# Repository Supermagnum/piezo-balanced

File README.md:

A small board that uses a LSK389B dual N channel Jfet,and a LSK170B N channel Jfet for preamplifier and impedance matching of two piezo electric crystals wired in balance.
Those J-FET's are ultra low noise components.
Please use 0,5 W metal film resistors with 1% tolerance or better and audio quality capacitors.
C0G (NP0) or X7R capacitors is very good.

The circuit may benefit from a Zobel network, that is a 680 pF capacitor and a 150 ohms resistor in series between pin 2 and 3 on the output or the input connector. It should avoid high frequency oscillation in a long cable.

It has balanced input and output.
That should minimize electric noise picked up from the environment.
One can read more about that here:
https://en.m.wikipedia.org/wiki/Balanced_audio

It's for +48 volt phantom power.
https://en.m.wikipedia.org/wiki/Phantom_power

+48 volt phantom power supply with mono headphone jack, runs on 9V battery:
https://github.com/Supermagnum/48power

PCB:
https://aisler.net/p/UJQSALGW
Note: Aisler does not carry LSK170B in  TO-92 3L or LSK389B in TO-71-6 .

PCB dimentions:
https://github.com/Supermagnum/piezo-balanced/blob/main/dimentions.png

Component side picture:
https://raw.githubusercontent.com/Supermagnum/piezo-balanced/main/piezo-jfet.jpg

Back side picture:
https://github.com/Supermagnum/piezo-balanced/raw/main/piezo-jfet2.jpg

Electronic diagram with component values, it also shows how to wire the crystals:
https://github.com/Supermagnum/piezo-balanced/blob/main/piezo-jfet.pdf

Gerber files for production of the PCB:
https://github.com/Supermagnum/piezo-balanced/tree/main/gerbers

Simulation in Ltspice:

Ltspice setup:
https://github.com/Supermagnum/piezo-balanced/blob/main/Ltspice-setup.png

Frequency response:
https://github.com/Supermagnum/piezo-balanced/blob/main/response.png

LSK170B datasheet:
https://www.linearsystems.com/lsdata/datasheets/201110%20-LSK170%20Rev%20A17%20dated%202017%2008%2028.pdf

Complete LSK389B datasheet:
https://linearsystems.com/lsdata/datasheets/Copy_201122%20-%20LSK389%20Datasheet%20Rev%20A24%202020%2001%2007.pdf

Digikey does not sell LSK389B or LSK170B in single or dual orders.
The 40 ohm resistor is also not sold by digikey .
Alternatively two 80 ohm resistors in parallel can be used.
That gives 40 ohm.

But, these does have LSK389B !
https://store.nacsemi.com/Products/Detail?stock=LIS000000001342

LSK170B:
https://store.nacsemi.com/products/detail?part=LSK170B-TO-92&stock=LIS000000000640

Picture of a piezoelectric disc, with red wire for positive polarity and black for negative:
https://github.com/Supermagnum/piezo-balanced/blob/main/Piezo-element-6.jpg

Why: 
The problem with piezo guitar pickups and piezoelectric crystals is that they are not well matched to typical audio inputs.
By their nature they can generate a lot of signal, but they cannot drive a 50 kilohm typical line input. 
The pickup needs to work into a much higher impedance, typically 1 megohm or so.

So what to people do? 
They go and plug a piezoelectric disks output directly into the line input of their recorder, 
typical impedance 50k, or the plug-in-power mic input of their recorder, typical impedance about 7k,
and they start to bitch and moan that this damn thing sounds tinny. 
Which is does ! But they don't understand why!

The reason why these devices often sound tinny is because the piezo sensor 
presents its signal through a series capacitance which is small, typically 15nF or less. 
When wired to a normal 50 kilohm line input this forms a high-pass filter, which eliminates the bass.

This circuit board solves that, and amplifies the signal around 15~30 dB. 
How many dB it amplifies is dependent on the impedance on the recording equipment.

I am getting 24 dB with 10K ohm impedance of the recorder ( simulated ).

If R4, R8 and R12 is removed,and jumpers installed in their place, the gain is 38 dB with 10K impedance.
You get more with higher impedance, expect 40 dB with 40K impedance of the recorders input.

It's fairly easy and straight forward to solder the components to the circuit board,
a nice pointy soldering iron, solder, a magnifying glass, and a ohm or multimeter is all that is needed.
Of course one needs a suitable metal box, and the circuit boards components
must not come in contact with the metal box. 
That will cause short circuit, so it's best mounted on stand offs.
Also, use the magnifying glass to check that no one of the soldering pads has been bridged.

It can be used for a reverb plate, listening to the insides of a engine,recording the sound of vibrating things.
You will need two piezoelectric disks for that, mounted in a metal box. 
Non electric conductive super glue is useable for that. Just glue them to a flat surface.
The piezoelectric disks should be electrically insulated from the metal box.

Mechanics may even use it to discover trouble with bearings or other mechanisms not easily opened,
but it will need a dedicated +48 volts phantom power supply with headphone jack for that specific usage. 

Of course one can use a recorder like a tascam dr40x, as long as it can supply +48 volt phantom power, and has a headphone jack for monitoring.

They usually have a 3 pin XLR plug.
Those are wired up like this:
https://github.com/Supermagnum/piezo-balanced/blob/main/XLR%2BConnector%2BPinout%2BDiagram%2BRear%2BPin%2B2%2BHot%2Bv2%2Bgreen__01.jpg

NOTE:  
The XLR 3 pin plug has a solder lug for the shield for a reason.
It is my opinion that a shielded cable with 3 conductors inside is the best.
Suggested cable: Digi-Key Part Number: 30-00910-5-ND

A good set of headphones or ear protection with built in speakers will keep out unwanted sounds or noise.

Should also work nice with hydrophones.
PZT-5H tubes is best for that.

For hydrophone usage:
The two piezoelectric tubes elements needs to be encapsulated in Ecopoxy Flowcast epoxy, with as little thickness to the outside of the piezoelectric tubes as possible. 
Commercial ones uses kerosene oil, so olive oil or sunflower oil is a great alternative as it will not pollute the environment if any leaks occurs.
A streamlined bulb should be nice for that. The more streamlined, the less water flow noise. 

Some interesting ideas can be found in:
https://github.com/Supermagnum/piezo-balanced/blob/main/Barlow-et-al-2008-HydrophoneConstruction_TM-417.pdf
Note: Ecopoxy Flowcast does not need any vacuum, just a mold and a way to hold the piezoelectric tubes centered.
It's also safer to work with.
Of course two piezoelectric disks inside something waterproof that can handle the water pressure is also useable.

Some methods of mounting a piezoelectric disk can be found here: https://locusonus.org/wiki/index.php?page=Hydrophone.en

Made with:
http://www.kicad.org/

KiCad uses an integrated environment for all of the stages of the design process: Schematic capture, PCB layout, Gerber file generation/visualization, and library editing.

KiCad is a cross-platform program, and of curse free!

The PCB board is tested and works.

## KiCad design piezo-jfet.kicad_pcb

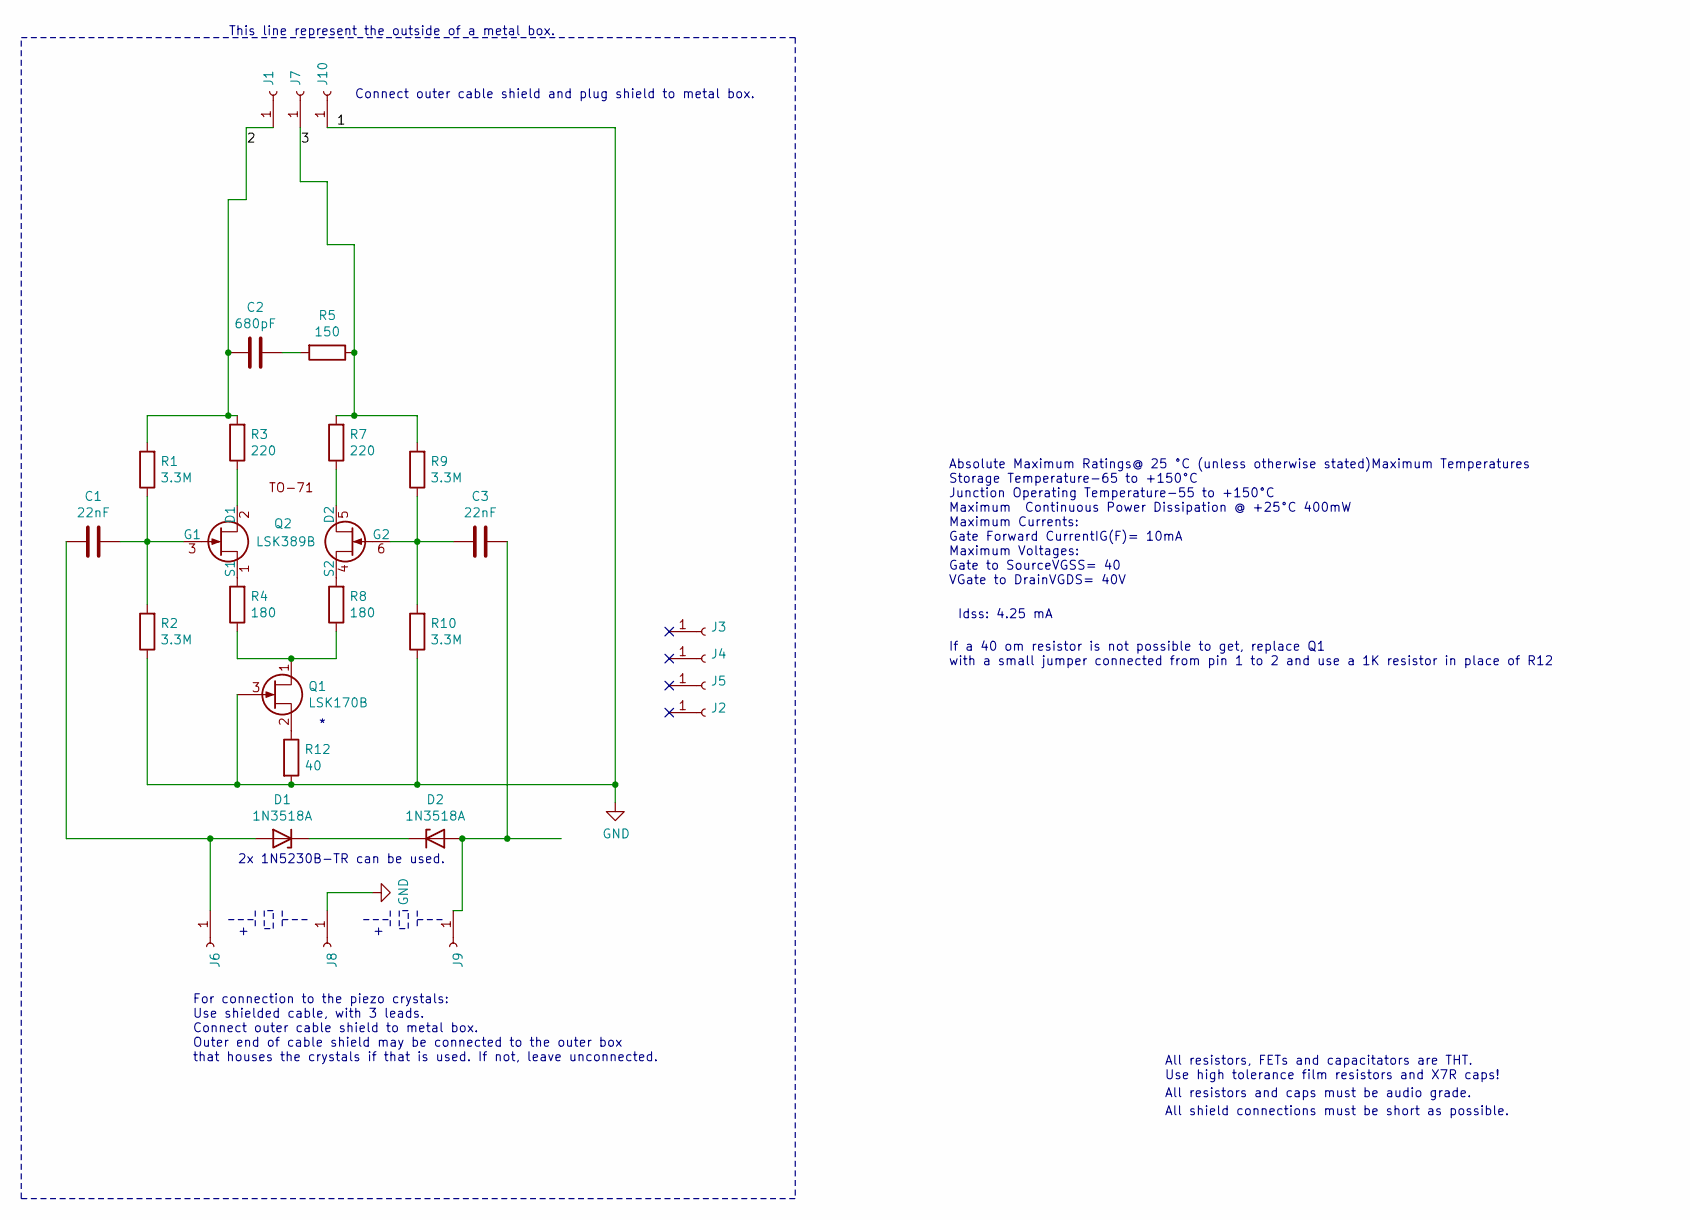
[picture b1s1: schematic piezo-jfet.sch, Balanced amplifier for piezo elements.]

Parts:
C1, C3: 22nF; C_Disc_D3.0mm_W2.0mm_P2.50mm
C2: 680pF; C_Disc_D3.0mm_W2.0mm_P2.50mm
D1, D2: 1N3518A; D_DO-35_SOD27_P7.62mm_Horizontal
J1, J2, J3, J4, J5, J6, J7, J8, J9, J10: Conn_01x01_Female; MountingHole_2.2mm_M2_DIN965_Pad
Q1: LSK170B; TO-92_Inline
Q2: LSK389B; TO-71-6
R1, R2, R9, R10: 3.3M; R_Axial_DIN0204_L3.6mm_D1.6mm_P5.08mm_Horizontal
R3, R7: 220; R_Axial_DIN0204_L3.6mm_D1.6mm_P5.08mm_Horizontal
R4, R8: 180; R_Axial_DIN0204_L3.6mm_D1.6mm_P5.08mm_Horizontal
R5: 150; R_Axial_DIN0204_L3.6mm_D1.6mm_P5.08mm_Horizontal
R12: 40; R_Axial_DIN0204_L3.6mm_D1.6mm_P5.08mm_Horizontal

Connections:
/2: C2.2, J1.1, R1.2, R3.2
/3: J7.1, R5.1, R7.2, R9.2
GND: J8.1, J10.1, Q1.3 (G), R2.1, R10.1, R12.2
unnamed: C1.1, Q2.3 (G1), R1.1, R2.2
unnamed: C1.2, D1.2 (A), J6.1
unnamed: C2.1, R5.2
unnamed: C3.1, D2.2 (A), J9.1
unnamed: C3.2, Q2.6 (G2), R9.1, R10.2
unnamed: D1.1 (K), D2.1 (K)
unnamed: Q1.1 (D), R4.1, R8.1
unnamed: Q1.2 (S), R12.1
unnamed: Q2.1 (S1), R4.2
unnamed: Q2.2 (D1), R3.1
unnamed: Q2.4 (S2), R8.2
unnamed: Q2.5 (D2), R7.1

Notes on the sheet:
Connect outer cable shield and plug shield to metal box.
For connection to the piezo crystals: Use shielded cable, with 3 leads. Connect outer cable shield to metal box. Outer end of cable shield may be connected to the outer box that houses the crystals if that is used. If not, leave unconnected.
This line represent the outside of a metal box.
All resistors, FETs and capacitators are THT. Use high tolerance film resistors and X7R caps!
2x 1N5230B-TR can be used.
Absolute Maximum Ratings@ 25 °C (unless otherwise stated)Maximum Temperatures Storage Temperature-65 to +150°C Junction Operating Temperature-55 to +150°C Maximum Continuous Power Dissipation @ +25°C 400mW Maximum Currents: Gate Forward CurrentIG(F)= 10mA Maximum Voltages: Gate to SourceVGSS= 40 VG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
Idss: 4.25 mA
All resistors and caps must be audio grade.
All shield connections must be short as possible.
If a 40 om resistor is not possible to get, replace Q1 with a small jumper connected from pin 1 to 2 and use a 1K resistor in place of R12

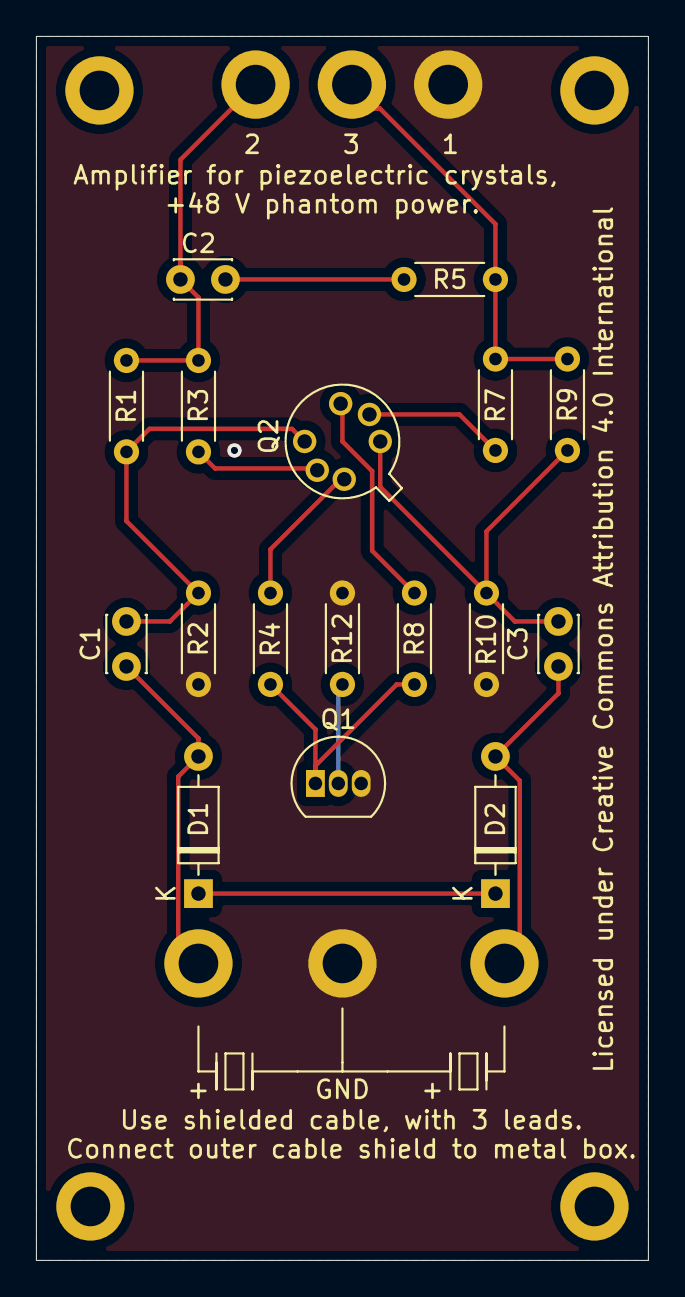
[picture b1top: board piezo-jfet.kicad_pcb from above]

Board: 2 copper layers, 34.0 x 68.0 mm, 27 parts (0 on the bottom side), 15 nets.

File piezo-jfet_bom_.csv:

Component,Description,Part,References,Value,Footprint,Quantity Per PCB,Datasheet
1,Unpolarized capacitor,C,C2,680pF,C_Disc_D3.0mm_W2.0mm_P2.50mm,1,~
2,Unpolarized capacitor,C,C1 C3,22nF,C_Disc_D3.0mm_W2.0mm_P2.50mm,2,~
3,Zener diode,D_Zener,D1 D2,1N3518A,D_DO-35_SOD27_P7.62mm_Horizontal,2,~
4,"XLR Connector, Male or Female, 3 Pins",XLR3,J1,XLR3,PinSocket_1x03_P2.54mm_Vertical,1, ~
5,"N-JFET transistor, drain/source/gate",Q_NJFET_DSG,Q1,J105,TO-92_Inline,1,~
6,,LSK389-Teensy,Q2,LSK389B,TO-71-6,1,https://www.linearsystems.com/lsdata/datasheets/Copy_201122%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
7,Resistor,R,R6,150,R_Axial_DIN0204_L3.6mm_D1.6mm_P5.08mm_Horizontal,1,~
8,Resistor,R,R4 R8,180,R_Axial_DIN0204_L3.6mm_D1.6mm_P5.08mm_Horizontal,2,~
9,Resistor,R,R3 R7,220,R_Axial_DIN0204_L3.6mm_D1.6mm_P5.08mm_Horizontal,2,~
10,Resistor,R,R12,270,R_Axial_DIN0204_L3.6mm_D1.6mm_P5.08mm_Horizontal,1,~
11,Resistor,R,R1 R2 R9 R10,3.3M,R_Axial_DIN0204_L3.6mm_D1.6mm_P5.08mm_Horizontal,4,~
12,,XTAL-Keyboard,X1 X2,XTAL,PinSocket_1x02_P2.54mm_Vertical,2,





Component Groups:,12
Component Count:,20
Fitted Components:,20
Number of PCBs:,1
Total components:,20
Schematic Version:,
Schematic Date:,
PCB Variant:,default
BoM Date:,ma. 17. mai 2021 kl. 13.42 +0200
Schematic Source:,piezo-jfet.sch
KiCad Version:,Eeschema 5.1.10

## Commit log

2021-05-16 Add files via upload
    added gerber files
2021-05-16 Add files via upload
    added more files
2021-05-18 Add files via upload
    Updated files.
2021-05-18 Add files via upload
    Added wiring for piezoelectric elements.
2021-05-18 Update README.md
    Updated readme
2021-05-21 updated files
2021-05-21 Add files via upload
    updated
2021-06-01 Update README.md
    Added links to pictures.
2021-06-01 Add files via upload
    added note on pdf.
2021-06-01 Add files via upload
    updated gerbers.
2021-06-06 Update README.md
    Updated with information on where to get LSK170B .
2021-06-07 Update README.md
    added frequency response.
2021-06-07 Update README.md
    Fixed wording.
2021-06-08 Update README.md
    Added clarification
2021-06-09 Update README.md
    Clarification of text.
2021-06-09 Update README.md
    Updated text.
2021-06-15 Uploaded in case it gets lost from the internets.
2021-06-19 Update README.md
    Corrected typo.
2021-07-02 Update README.md
    Cleanup text.

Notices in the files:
piezo-jfet.kicad_pcb:
Licensed under Creative Commons Attribution 4.0 International
